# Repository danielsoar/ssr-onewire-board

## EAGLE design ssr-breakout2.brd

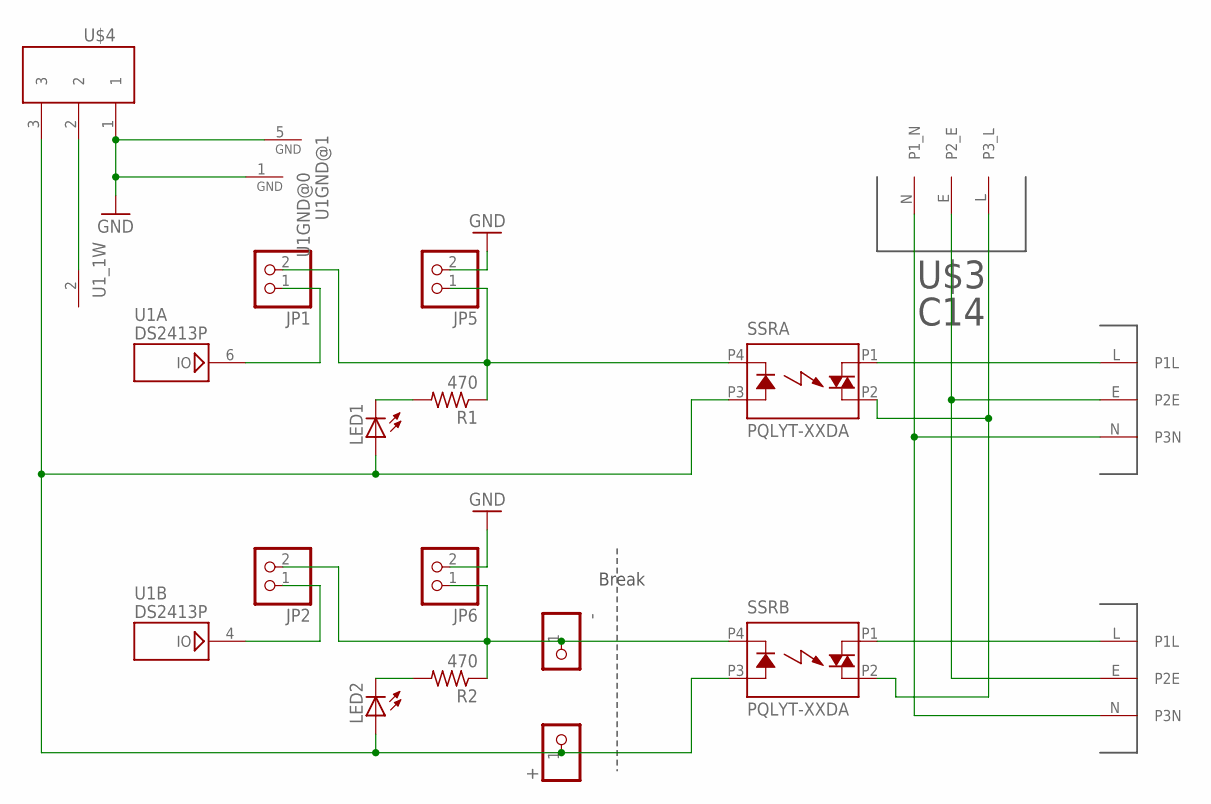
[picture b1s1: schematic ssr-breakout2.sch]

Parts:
+: PINHD-1X1CB; 1X01-CLEANBIG
-: PINHD-1X1CB; 1X01-CLEANBIG
JP1, JP2, JP5, JP6: PINHD-1X2; 1X02
LED1, LED2: LEDCHIPLED_0805; CHIPLED_0805
R1, R2: 470; R0805
SSRA: PQLYT-XXDA; PQLYT
SSRB: PQLYT-XXDA; PQLYT
U1: DS2413P; TSOC6
U$3: C14; 6ESRM-P
U$4: 3.5MM3PHORIZONTAL; 3.5MM3P
U$5, U$6: C13; PX0695/10/PC

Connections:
GND: JP5.2, JP6.2, U1.1 (GND), U1.5 (GND), U$4.1
unnamed: LED1.C, R1.2
unnamed: LED2.C, R2.2
unnamed: -.1, JP2.2, JP6.1, R2.1, SSRB.P4 (K)
unnamed: +.1, LED1.A, LED2.A, SSRA.P3 (A), SSRB.P3 (A), U$4.3
unnamed: SSRA.P1 (DS1), U$5.L (P1L)
unnamed: SSRA.P2 (DS2), SSRB.P2 (DS2), U$3.L (P3_L)
unnamed: U1.2 (1W), U$4.2
unnamed: U$3.E (P2_E), U$5.E (P2E), U$6.E (P2E)
unnamed: SSRB.P1 (DS1), U$6.L (P1L)
unnamed: JP1.1, U1.6 (IO)
unnamed: JP2.1, U1.4 (IO)
unnamed: U$3.N (P1_N), U$5.N (P3N), U$6.N (P3N)
unnamed: JP1.2, JP5.1, R1.1, SSRA.P4 (K)

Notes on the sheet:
Break

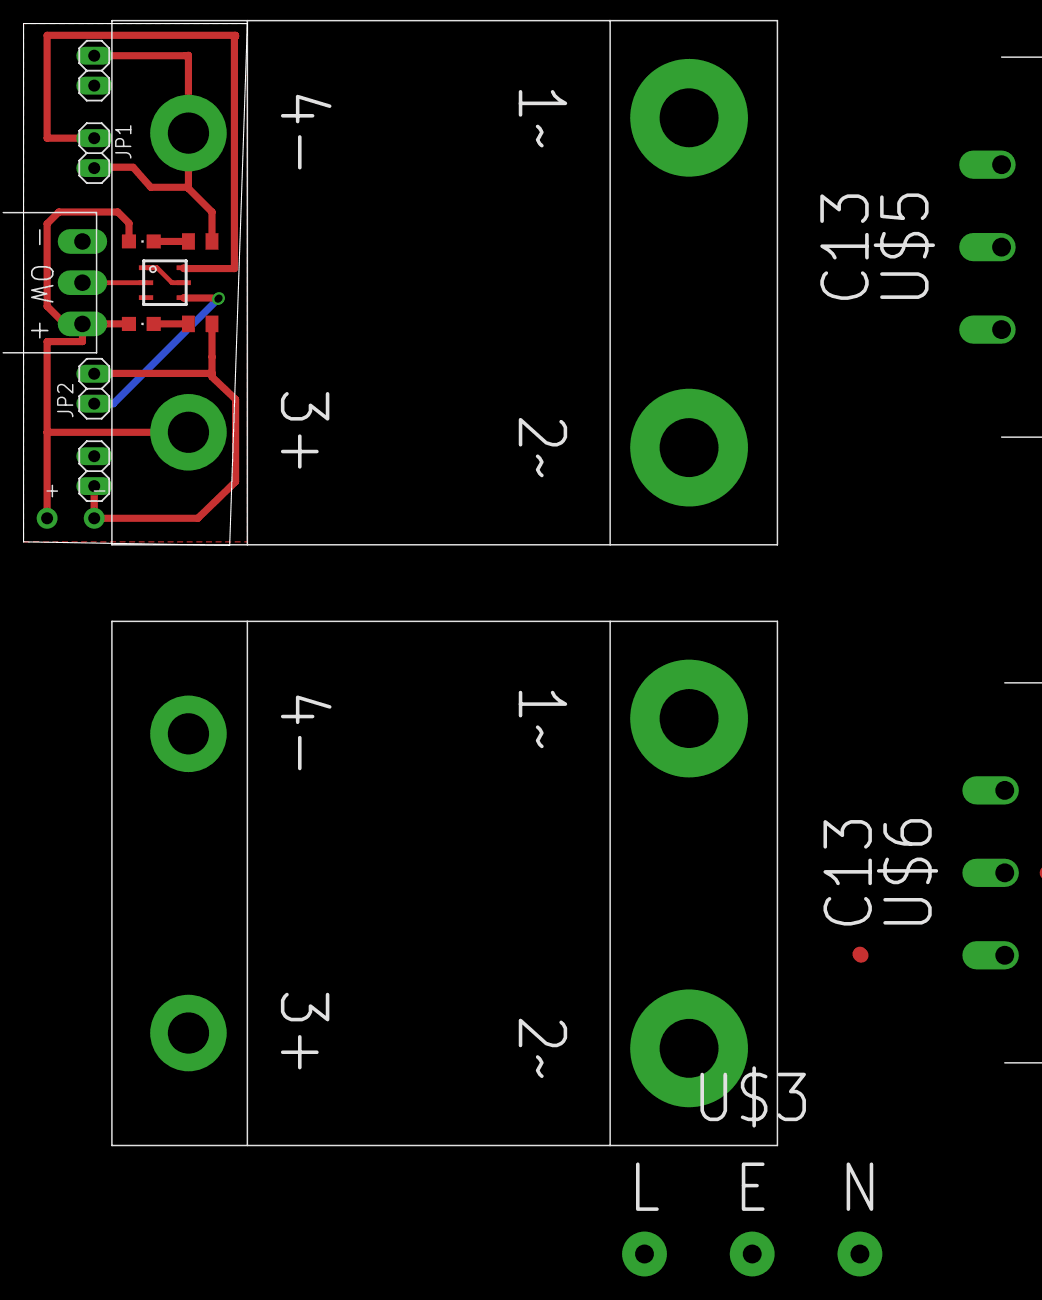
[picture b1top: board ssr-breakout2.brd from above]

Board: 2 copper layers, 17 parts (0 on the bottom side), 14 nets.

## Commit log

2014-03-13 Added isolation jumpers, removed AC side PCB in favour of harness.
    Added JP1/2 for isolating the output. These can be renamed if these
    labels are reserved for another jumper elsewhere in the project.
    Thoughts here are that there could be a three way selector switch.
    Off-Auto-On
    The Off position would actuate a normally closed switch that opens in
    this position. The on switch would actuate a normally open switch that
